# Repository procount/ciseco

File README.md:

# ciseco
Ciseo XRF documentation from the wirelessthings.net website, which has sadly closed.

Cisecostuff-2013 fodler kindly provided by Alvar Kusma
Alvar Kusma <alvar@raamat.polva.ee>

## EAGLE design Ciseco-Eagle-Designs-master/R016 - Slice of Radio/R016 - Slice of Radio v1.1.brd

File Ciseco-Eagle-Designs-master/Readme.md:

This repository contains the schematic and pcb files for some Ciseco products

Each product is in its own folder and there may be any combination of files from.
* PDF schematic
* Eagle schematic
* Eagle PCB
* Gerbers

If you wish to download all the files either use git clone

    $ git clone https://github.com/CisecoPlc/Ciseco-Eagle-Designs.git

or download them all as zip file

https://github.com/CisecoPlc/Ciseco-Eagle-Designs/archive/master.zip

To download individual files navigate to the file and select 'Raw' from the toolbar, then use your browsers File->Save As option

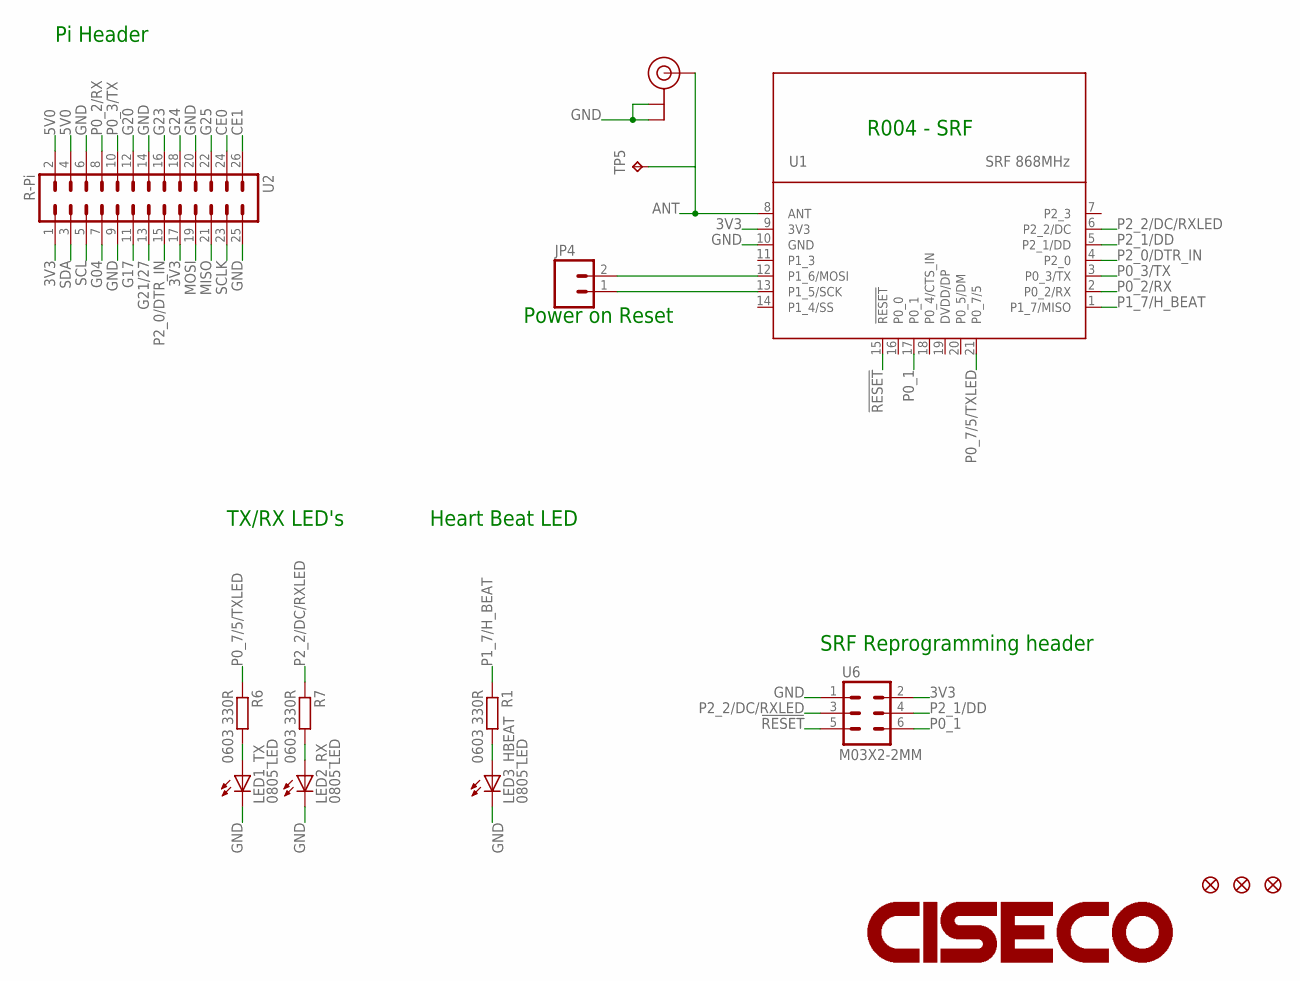
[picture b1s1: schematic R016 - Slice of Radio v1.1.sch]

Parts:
JP1, JP2, JP3: FIDUCIAL1X2.5-STOP; FIDUCIAL-1X2.5-STOP
JP4: M02PTH; 1X02
LED1_TX, LED2_RX, LED3_HBEAT: 0805 LED; LED-0805-CORRECT
LOGO1: CISECOLOGO-2MM; CISECO-2MM
R1, R6, R7: 0603 330R; C0603K-SMALL
TP5: TPPAD1-13; P1-13
U1: SRF 868MHz; SRF-LANDING-1.2
U2: R-Pi; EVE-BOARD-REF-LOCK
U6: M03X2-2MM; 2X3_2MM
U11: U.FL 868; U.FL

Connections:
3V3: U1.9 (3V3), U2.1, U2.17, U6.2
5V0: U2.2, U2.4
!RESET: U1.15 (!RESET), U6.5
ANT: TP5.TP, U1.8 (ANT), U11.P$3 (SIGNAL)
CE0: U2.24
CE1: U2.26
G04: U2.7
G17: U2.11
G20: U2.12
G21/27: U2.13
G23: U2.16
G24: U2.18
G25: U2.22
GND: LED1_TX.C, LED2_RX.C, LED3_HBEAT.C, U1.10 (GND), U2.6, U2.9, U2.14, U2.20, U2.25, U6.1, U11.P$1 (GND), U11.P$2 (GND)
MISO: U2.21
MOSI: U2.19
unnamed: LED3_HBEAT.A, R1.2
unnamed: JP4.1, U1.13 (P1_5/SCK)
unnamed: JP4.2, U1.12 (P1_6/MOSI)
unnamed: LED2_RX.A, R7.2
unnamed: LED1_TX.A, R6.2
P0_1: U1.17 (P0_1), U6.6
P0_2/RX: U1.2 (P0_2/RX), U2.8
P0_3/TX: U1.3 (P0_3/TX), U2.10
P0_7/5/TXLED: R6.1, U1.21 (P0_7/5)
P1_7/H_BEAT: R1.1, U1.1 (P1_7/MISO)
P2_0/DTR_IN: U1.4 (P2_0), U2.15
P2_1/DD: U1.5 (P2_1/DD), U6.4
P2_2/DC/RXLED: R7.1, U1.6 (P2_2/DC), U6.3
SCL: U2.5
SCLK: U2.23
SDA: U2.3

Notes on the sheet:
Power on Reset
Pi Header
SRF Reprogramming header
TX/RX LED's
Heart Beat LED
R004 - SRF

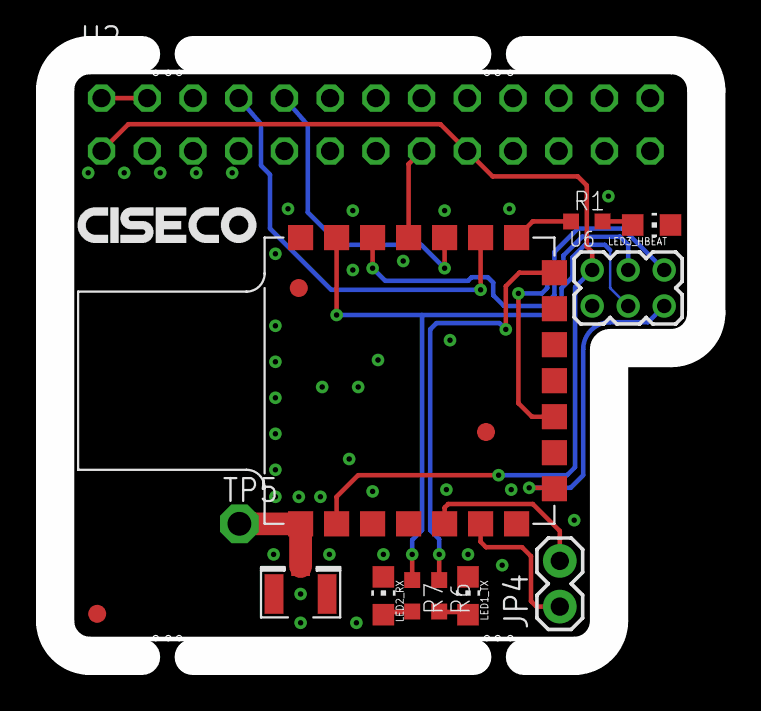
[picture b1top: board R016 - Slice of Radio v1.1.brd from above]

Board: 2 copper layers, 36.3 x 33.5 mm, 18 parts (1 on the bottom side), 18 nets.

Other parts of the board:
U$4: WEEE-LOGO
U$5: PIBOW

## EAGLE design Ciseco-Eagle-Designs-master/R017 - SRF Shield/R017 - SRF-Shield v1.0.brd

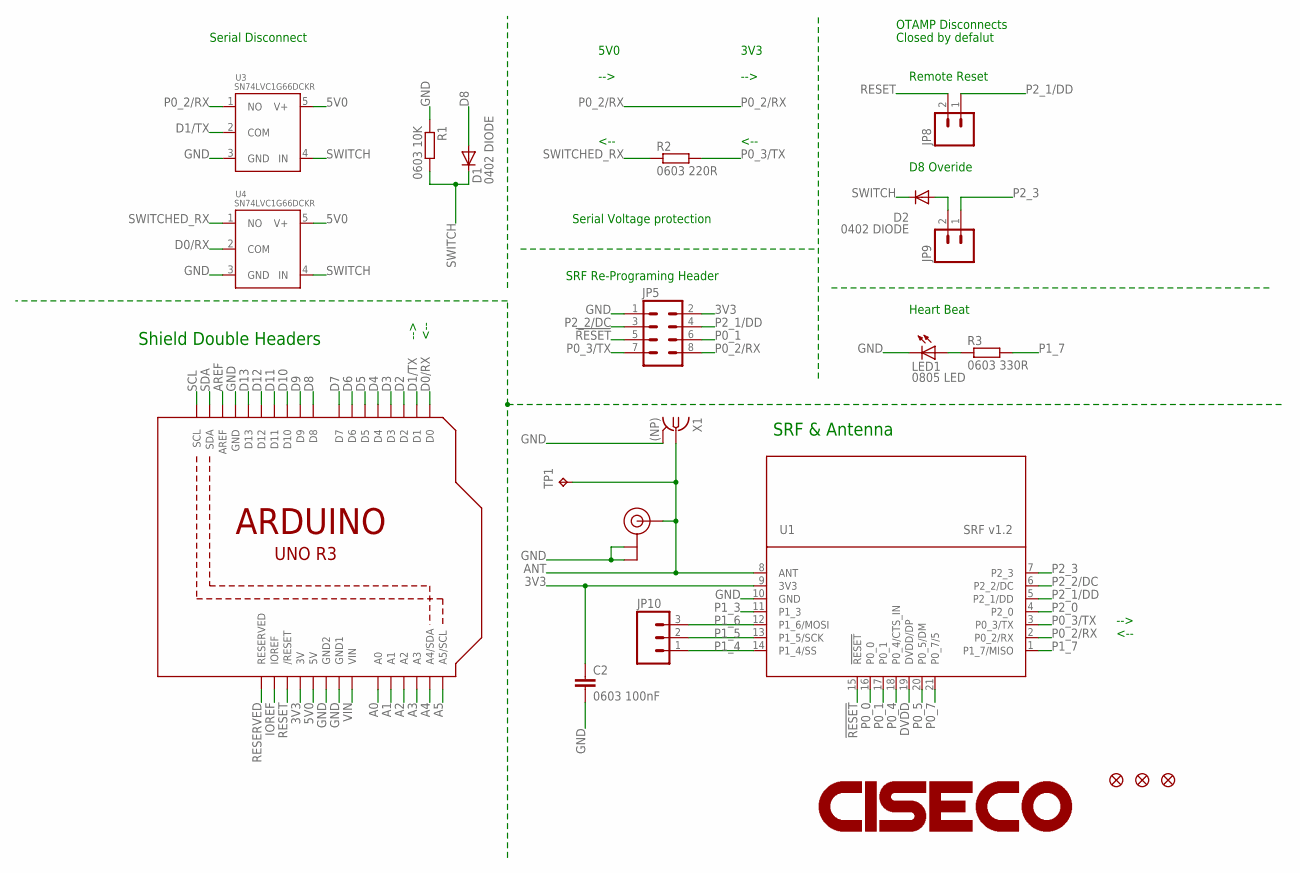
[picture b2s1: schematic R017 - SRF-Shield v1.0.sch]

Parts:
C2: 0603 100nF; C0402-NARROW
D1, D2: 0402 DIODE; D0402-NARROW
JP4, JP6, JP7: FIDUCIAL1X2.5-STOP; FIDUCIAL-1X2.5-STOP
JP5: M04X2; 2X4
JP8, JP9: M02PTH; 1X02
JP10: M03PTH; 1X03
LED1: 0805 LED; LED-0805-1206
R1: 0603 10K; C0603K-SMALL
R2: 0603 220R; C0603K-SMALL
R3: 0603 330R; C0603K-SMALL
TP1: TPPAD1-13; P1-13
U1: SRF v1.2; SRF-LANDING-1.0A-MOVE
U2: ARDUINOR3-DOUBL-OFFSET; ARDUINOR3-DOUBLE-OFFSET
U3, U4: SN74LVC1G66DCKR; SC70
U5: U.FL (NP); U.FL
U$3: CISECO-LARGE; CISECO-4MM
X1: (NP); J502-ND-142-0711-821/826-LWK1

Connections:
3V3: C2.1, JP5.2, U1.9 (3V3), U2.3V, U2.3V1 (3V)
5V0: U2.5V, U2.5V1 (5V), U3.5 (V+), U4.5 (V+)
!RESET: JP5.5, U1.15 (!RESET)
A0: U2.A0, U2.A6 (A0)
A1: U2.A1, U2.A7 (A1)
A2: U2.A2, U2.A8 (A2)
A3: U2.A3, U2.A9 (A3)
A4: U2.A4 (A4/SDA), U2.A10 (A4/SDA)
A5: U2.A5 (A5/SCL), U2.A11 (A5/SCL)
ANT: TP1.TP, U1.8 (ANT), U5.P$3 (SIGNAL), X1.1
AREF: U2.AREF, U2.AREF1 (AREF)
D0/RX: U2.D0, U2.D18 (D0), U4.2 (COM)
D1/TX: U2.D1, U2.D17 (D1), U3.2 (COM)
D2: U2.D2, U2.D16 (D2)
D3: U2.D3, U2.D15 (D3)
D4: U2.D4, U2.D14 (D4)
D5: U2.D5, U2.D19 (D5)
D6: U2.D6, U2.D20 (D6)
D7: U2.D7, U2.D21 (D7)
D8: D1.A, U2.D8, U2.D22 (D8)
D9: U2.D9, U2.D23 (D9)
D10: U2.D10, U2.D24 (D10)
D11: U2.D11, U2.D25 (D11)
D12: U2.D12, U2.D26 (D12)
D13: U2.D13, U2.D27 (D13)
DVDD: U1.19 (DVDD/DP)
GND: C2.2, JP5.1, LED1.C, R1.1, U1.10 (GND), U2.GND, U2.GND1, U2.GND2, U2.GND3 (GND1), U2.GND4 (GND2), U2.GND5 (GND), U3.3 (GND), U4.3 (GND), U5.P$1 (GND), U5.P$2 (GND), X1.G@1 (GND), X1.G@2 (GND), X1.G@3 (GND), X1.G@4 (GND)
IOREF: U2.IOREF, U2.IOREF1 (IOREF)
unnamed: LED1.A, R3.1
OTAMP_M: D2.A, JP9.2
P0_0: U1.16 (P0_0)
P0_1: JP5.6, U1.17 (P0_1)
P0_2/RX: JP5.8, U1.2 (P0_2/RX), U3.1 (NO)
P0_3/TX: JP5.7, R2.2, U1.3 (P0_3/TX)
P0_4: U1.18 (P0_4/CTS_IN)
P0_5: U1.20 (P0_5/DM)
P0_7: U1.21 (P0_7/5)
P1_3: U1.11 (P1_3)
P1_4: JP10.1, U1.14 (P1_4/SS)
P1_5: JP10.2, U1.13 (P1_5/SCK)
P1_6: JP10.3, U1.12 (P1_6/MOSI)
P1_7: R3.2, U1.1 (P1_7/MISO)
P2_0: U1.4 (P2_0)
P2_1/DD: JP5.4, JP8.1, U1.5 (P2_1/DD)
P2_2/DC: JP5.3, U1.6 (P2_2/DC)
P2_3: JP9.1, U1.7 (P2_3)
RESERVED: U2.RESERVED, U2.RESERVED1 (RESERVED)
RESET: JP8.2, U2.RESET (/RESET), U2.RESET1 (/RESET)
SCL: U2.SCL, U2.SCL1 (SCL)
SDA: U2.SDA, U2.SDA1 (SDA)
SWITCH: D1.C, D2.C, R1.2, U3.4 (IN), U4.4 (IN)
SWITCHED_RX: R2.1, U4.1 (NO)
VIN: U2.VIN, U2.VIN1 (VIN)

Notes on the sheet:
SRF Re-Programing Header
5V0
3V3
Remote Reset
Heart Beat
Closed by defalut
OTAMP Disconnects
Serial Voltage protection
Serial Disconnect
<--
-->
D8 Overide
Shield Double Headers
SRF & Antenna

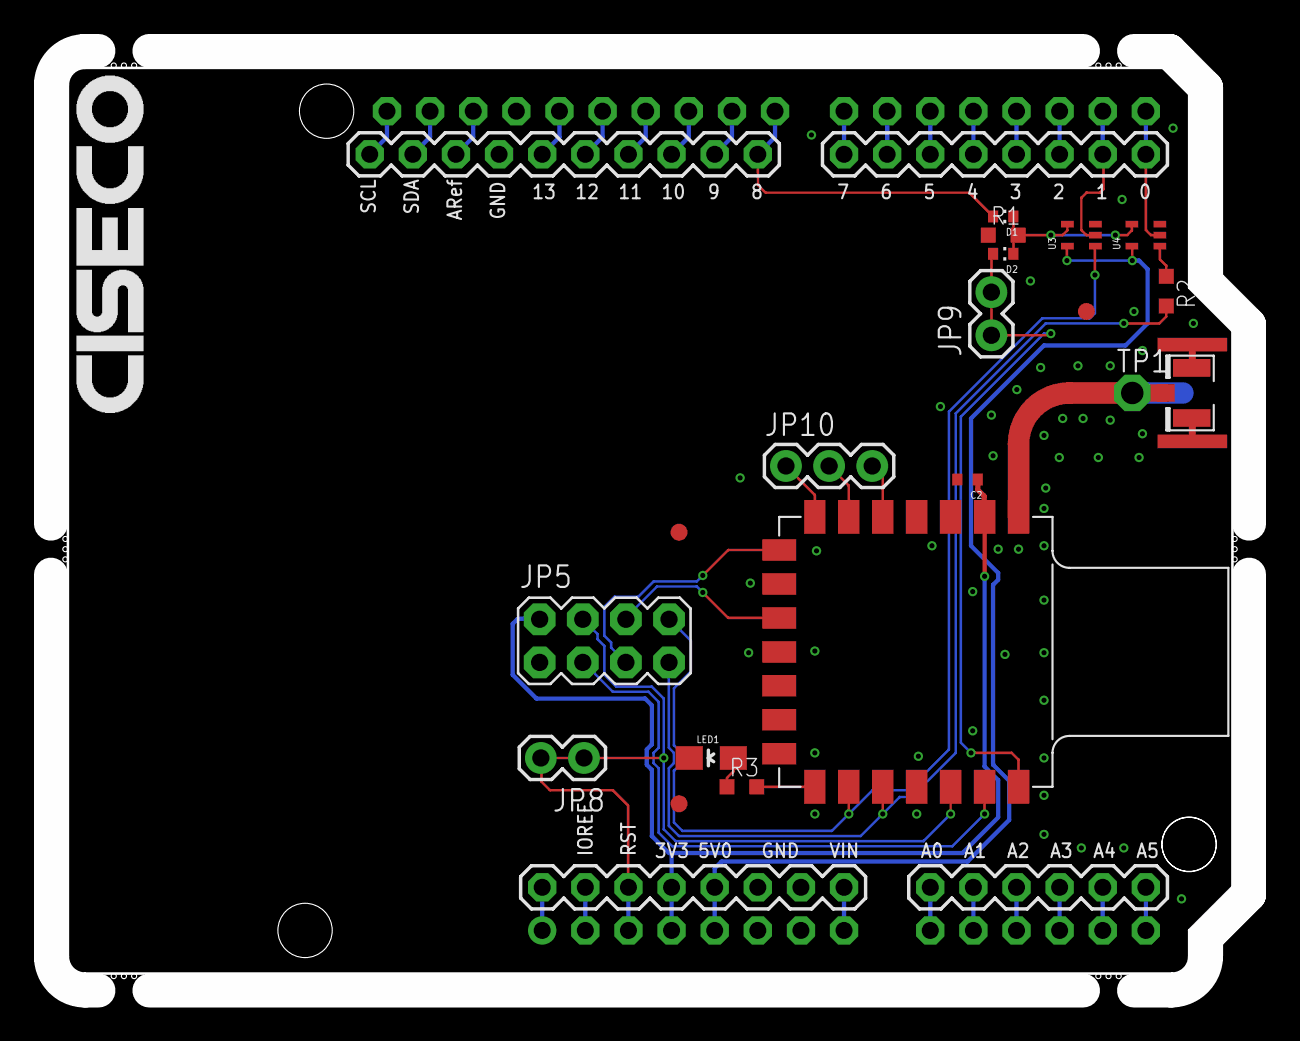
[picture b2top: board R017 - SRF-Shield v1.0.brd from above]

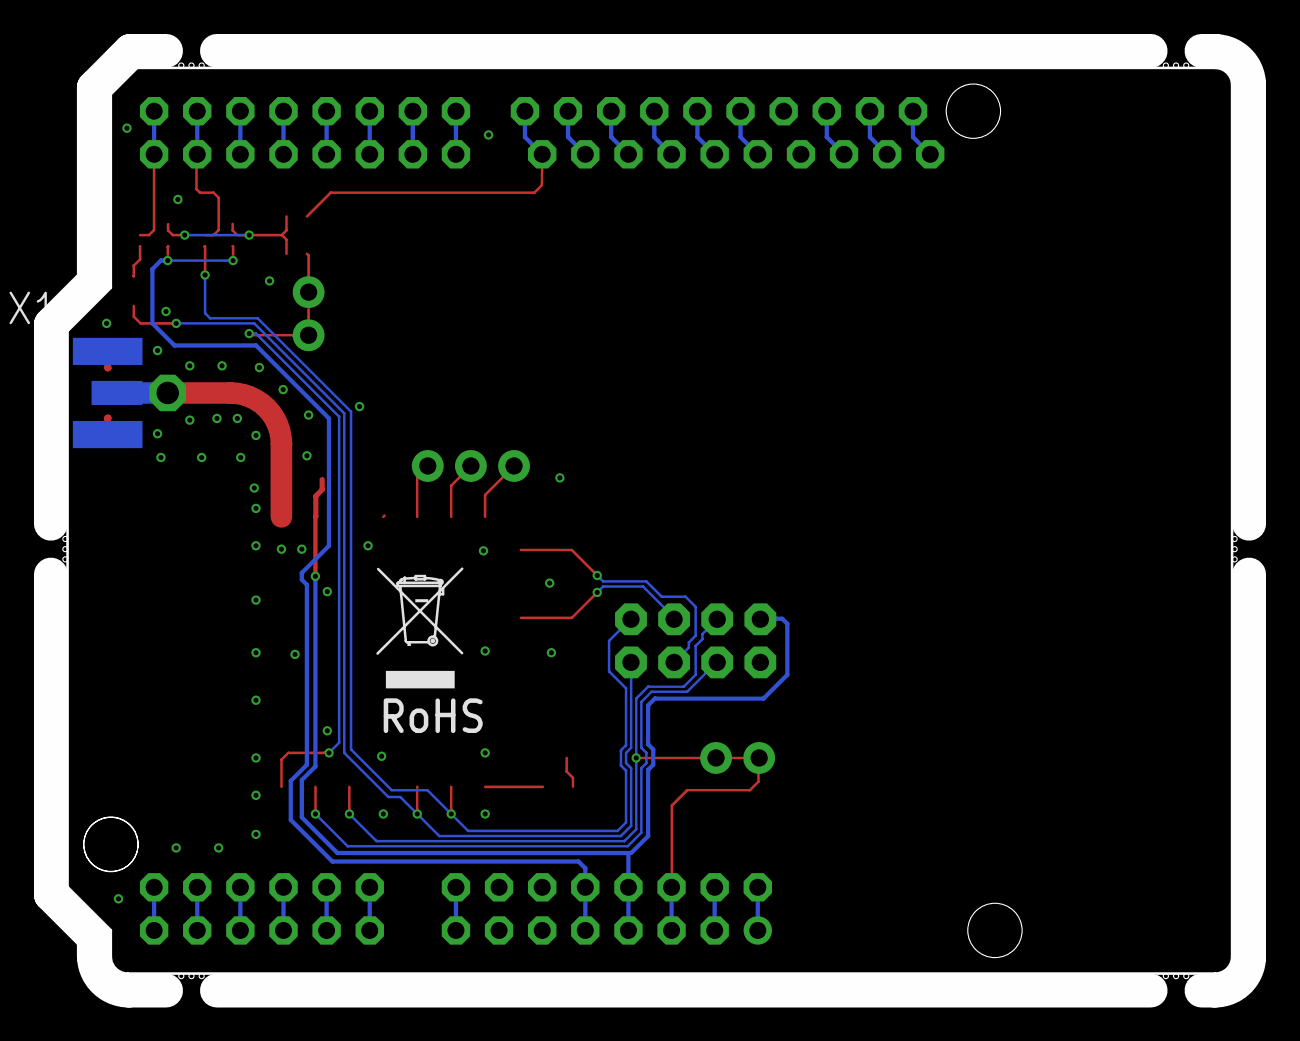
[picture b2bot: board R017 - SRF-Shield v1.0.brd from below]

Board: 2 copper layers, 70.6 x 55.4 mm, 23 parts (2 on the bottom side), 46 nets.

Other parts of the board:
U$6: WEEE-LOGO

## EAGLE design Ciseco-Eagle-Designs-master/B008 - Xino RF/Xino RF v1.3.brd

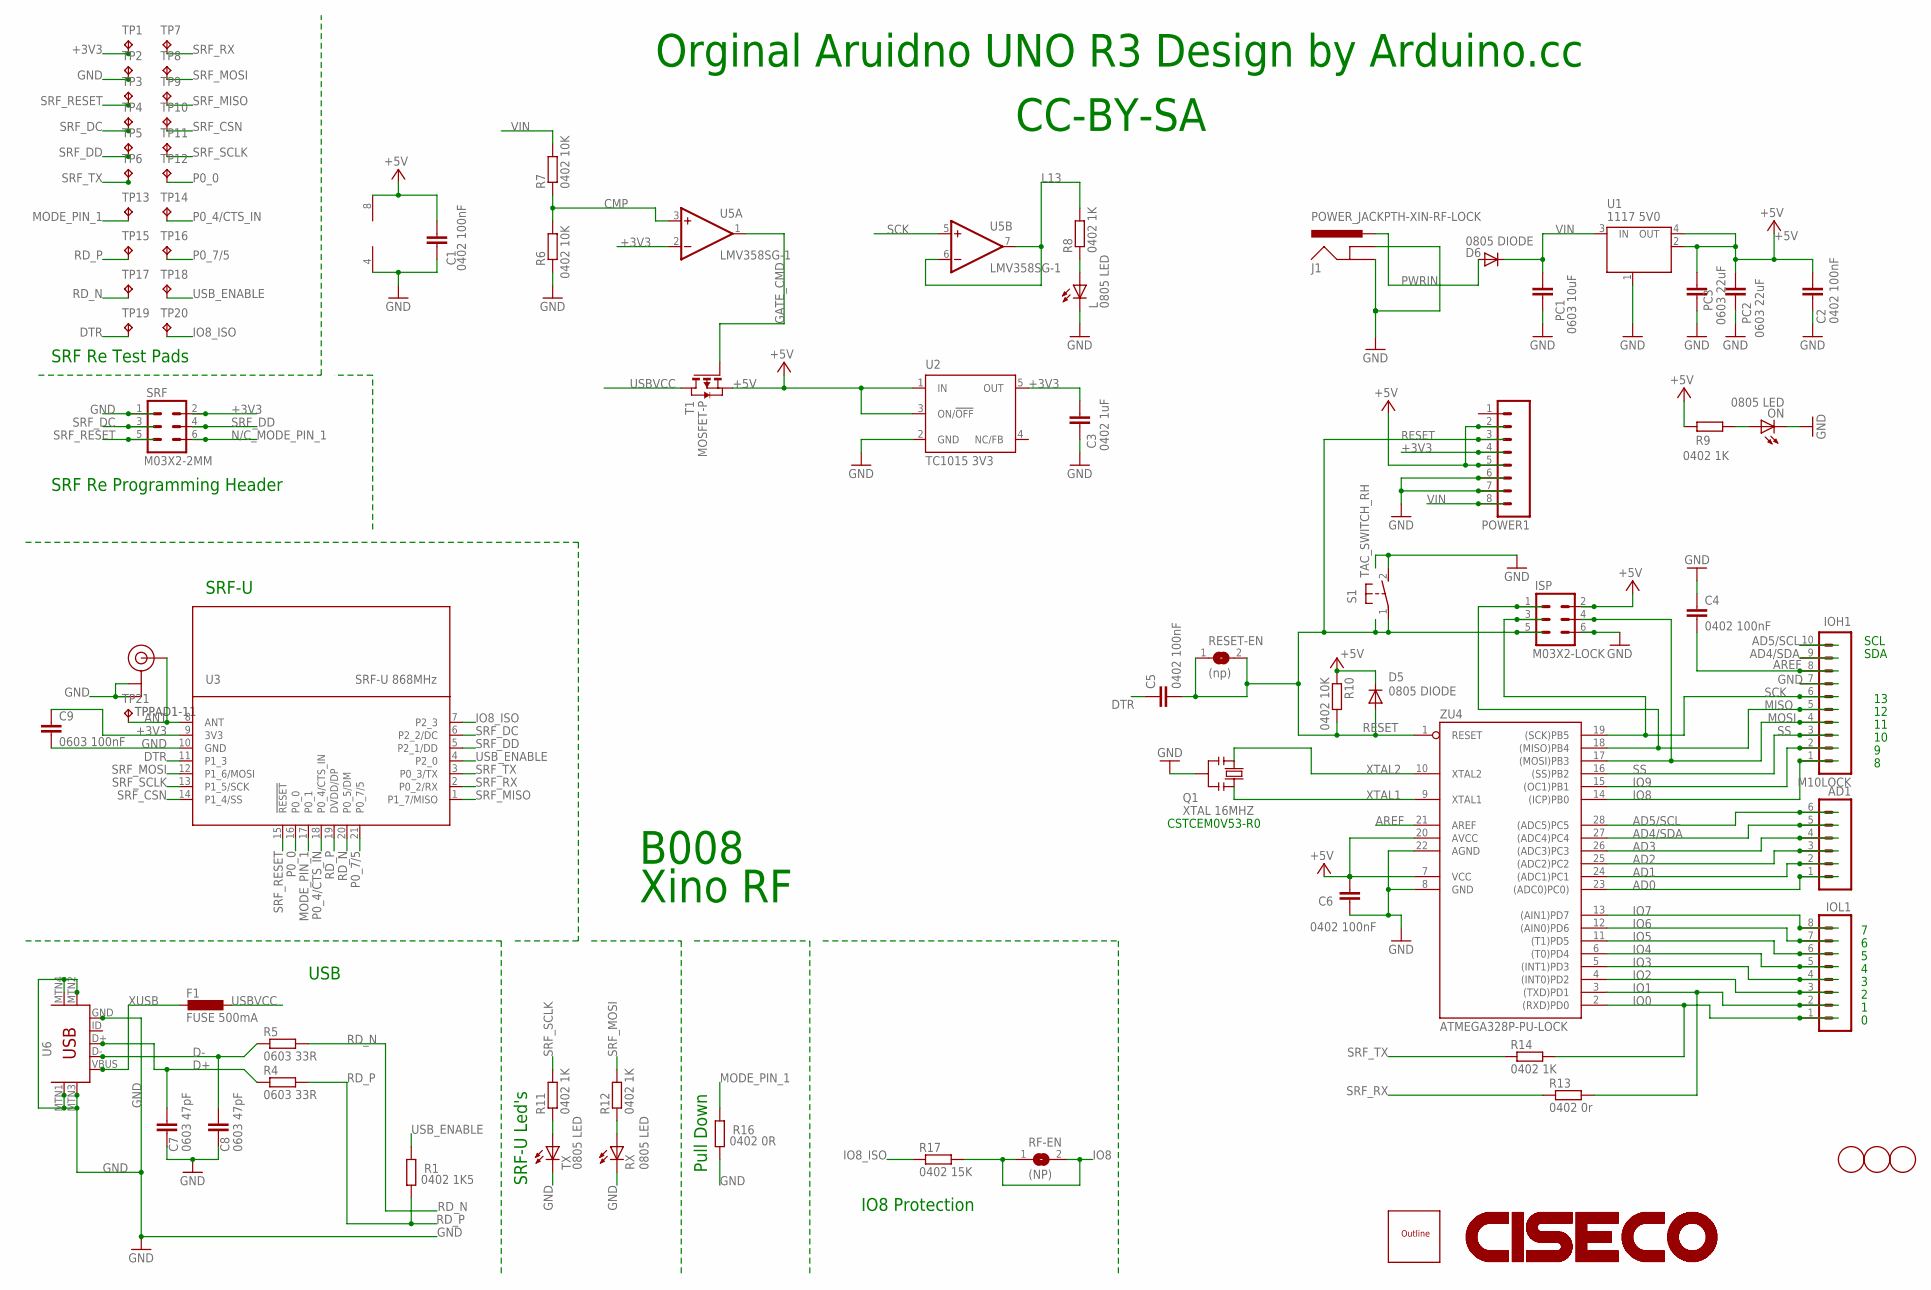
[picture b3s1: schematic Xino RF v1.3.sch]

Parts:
AD1: M06LOCK; 1X06_LOCK
C1, C2, C4, C5: 0402 100nF; C0402-SMALLER
C3: 0402 1uF; C0402-SMALLER
C6: 0402 100nF; C0603-ROUND
C7, C8: 0603 47pF; C0603K-SMALL
C9: 0603 100nF; C0402-SMALLER
D5, D6: 0805 DIODE; 0805-DIODE
F1: FUSE 500mA; L1812
FD1, FD2, FD3: FIDUCIALMOUNT; FIDUCIA-MOUNT
IOH1: M10LOCK; 1X10_LOCK
IOL1: M08LOCK; 1X08_LOCK
ISP: M03X2-LOCK; 2X3_LOCK
J1: POWER_JACKPTH-XIN-RF-LOCK; POWER_JACK_PTH_XINO_RF_LOCK
L: 0805 LED; LED-0805-1206
ON: 0805 LED; LED-0805-1206
PC1: 0603 10uF; C0805K
PC2, PC3: 0603 22uF; C0805K
POWER1: M08LOCK; 1X08_LOCK
Q1: XTAL 16MHZ; RESONATOR
R1: 0402 1K5; R0402-SMALLER
R4, R5: 0603 33R; C0603K-SMALL
R6, R7, R10: 0402 10K; R0402-SMALLER
R8, R9, R11, R12, R14: 0402 1K; R0402-SMALLER
R13: 0402 0r; R0402-SMALLER
R16: 0402 0R; R0402-SMALLER
R17: 0402 15K; R0402-SMALLER
RESET-EN: (np); SJ
RF-EN: (NP); SJ
RX: 0805 LED; LED-0805-1206
S1: TAC_SWITCH_RH; B3F-31XX
SRF: M03X2-2MM; 2X3_2MM
T1: MOSFET-P; SOT-23
TP1, TP2, TP3, TP4, TP5, TP6, TP7, TP8, TP9, TP10, TP11, TP12, TP13, TP14, TP15, TP16, TP17, TP18, TP19, TP20: TPB1,27; B1,27
TP21: TPPAD1-11; P1-11
TX: 0805 LED; LED-0805-1206
U1: 1117 5V0; SOT223
U2: TC1015 3V3; SOT23-DBV
U3: SRF-U 868MHz; SRF-LANDING-1.2
U5: LMV358SG-1; SO08
U6: USB-MINIB-5PIN; USB-MINIB-CISECO-1
U11: U.FL 868; U.FL
U$1: CISECO-MEDIUM; CISECO-1.3MM
U$2: ARDUINO-OUTLINE-MILL
U$3: CISECO-LARGE; CISECO-4MM
ZU4: ATMEGA328P-PU-LOCK; DIL28-3-LOCK

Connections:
+3V3: C3.2, C9.1, POWER1.4, SRF.2, TP1.TP, U2.5 (OUT), U3.9 (3V3), U5.2 (-IN)
+5V: C1.2, C2.2, C6.2, D5.C, ISP.2, PC2.1, PC3.1, POWER1.2, POWER1.5, R9.2, R10.1, T1.2 (S), U1.2 (OUT), U1.4 (OUT), U2.1 (IN), U2.3 (ON/!OFF), U5.8 (V+), ZU4.7 (VCC), ZU4.20 (AVCC)
AD0: AD1.1, ZU4.23 ((ADC0)PC0))
AD1: AD1.2, ZU4.24 ((ADC1)PC1)
AD2: AD1.3, ZU4.25 ((ADC2)PC2)
AD3: AD1.4, ZU4.26 ((ADC3)PC3)
AD4/SDA: AD1.5, IOH1.9, ZU4.27 ((ADC4)PC4)
AD5/SCL: AD1.6, IOH1.10, ZU4.28 ((ADC5)PC5)
ANT: TP21.TP, U3.8 (ANT), U11.P$3 (SIGNAL)
AREF: C4.2, IOH1.8, ZU4.21 (AREF)
CMP: R6.2, R7.1, U5.3 (+IN)
D+: C7.1, R4.1, U6.D+
D-: C8.1, R5.1, U6.D-
DTR: C5.1, TP19.TP, U3.11 (P1_3)
GATE_CMD: T1.3 (G), U5.1 (OUT)
GND: C1.1, C2.1, C3.1, C4.1, C6.1, C7.2, C8.2, C9.2, IOH1.7, ISP.6, J1.GND, J1.GNDBREAK, L.C, ON.C, PC1.2, PC2.2, PC3.2, POWER1.6, POWER1.7, Q1.2, R6.1, R16.1, RX.C, S1.2 (S), SRF.1, TP2.TP, TX.C, U1.1 (GND/ADJ), U2.2 (GND), U3.10 (GND), U5.4 (V-), U6.GND, U6.MTN1 (MTN2), U6.MTN2 (MTN3), U6.MTN3 (MTN1), U6.MTN4, U11.P$1 (GND), U11.P$2 (GND), ZU4.8 (GND), ZU4.22 (AGND)
IO0: IOL1.1, R14.2, ZU4.2 ((RXD)PD0)
IO1: IOL1.2, R13.2, ZU4.3 ((TXD)PD1)
IO2: IOL1.3, ZU4.4 ((INT0)PD2)
IO3: IOL1.4, ZU4.5 ((INT1)PD3)
IO4: IOL1.5, ZU4.6 ((T0)PD4)
IO5: IOL1.6, ZU4.11 ((T1)PD5)
IO6: IOL1.7, ZU4.12 ((AIN0)PD6)
IO7: IOL1.8, ZU4.13 ((AIN1)PD7)
IO8: IOH1.1, R17.2, RF-EN.1, RF-EN.2, ZU4.14 ((ICP)PB0)
IO8_ISO: R17.1, TP20.TP, U3.7 (P2_3)
IO9: IOH1.2, ZU4.15 ((OC1)PB1)
L13: R8.2, U5.6 (-IN), U5.7 (OUT)
MISO: IOH1.5, ISP.1, ZU4.18 ((MISO)PB4)
MODE_PIN_1: R16.2, TP13.TP, U3.17 (P0_1)
MOSI: IOH1.4, ISP.4, ZU4.17 ((MOSI)PB3)
unnamed: L.A, R8.1
unnamed: ON.A, R9.1
unnamed: R12.1, RX.A
unnamed: R11.1, TX.A
N/C_MODE_PIN_1: SRF.6
P0_0: TP12.TP, U3.16 (P0_0)
P0_4/CTS_IN: TP14.TP, U3.18 (P0_4/CTS_IN)
P0_7/5: TP16.TP, U3.21 (P0_7/5)
PWRIN: D6.A, J1.PWR
RD_N: R5.2, TP17.TP, U3.20 (P0_5/DM)
RD_P: R1.1, R4.2, TP15.TP, U3.19 (DVDD/DP)
RESET: C5.2, D5.A, ISP.5, POWER1.3, R10.2, RESET-EN.1, RESET-EN.2, S1.1, ZU4.1 (RESET)
SCK: IOH1.6, ISP.3, U5.5 (+IN), ZU4.19 ((SCK)PB5)
SRF_CSN: TP10.TP, U3.14 (P1_4/SS)
SRF_DC: SRF.3, TP4.TP, U3.6 (P2_2/DC)
SRF_DD: SRF.4, TP5.TP, U3.5 (P2_1/DD)
SRF_MISO: TP9.TP, U3.1 (P1_7/MISO)
SRF_MOSI: R12.2, TP8.TP, U3.12 (P1_6/MOSI)
SRF_RESET: SRF.5, TP3.TP, U3.15 (!RESET)
SRF_RX: R13.1, TP7.TP, U3.2 (P0_2/RX)
SRF_SCLK: R11.2, TP11.TP, U3.13 (P1_5/SCK)
SRF_TX: R14.1, TP6.TP, U3.3 (P0_3/TX)
SS: IOH1.3, ZU4.16 ((SS)PB2)
USBVCC: F1.1, T1.1 (D)
USB_ENABLE: R1.2, TP18.TP, U3.4 (P2_0)
VIN: D6.C, PC1.1, POWER1.8, R7.2, U1.3 (IN)
XTAL1: Q1.3, ZU4.9 (XTAL1)
XTAL2: Q1.1, ZU4.10 (XTAL2)
XUSB: F1.2, U6.VBUS

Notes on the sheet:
Xino RF
SDA
SCL
Pull Down
IO8 Protection
CC-BY-SA
Orginal Aruidno UNO R3 Design by Arduino.cc
USB
SRF Re Programming Header
SRF Re Test Pads
SRF-U
SRF-U Led's
B008
CSTCEM0V53-R0

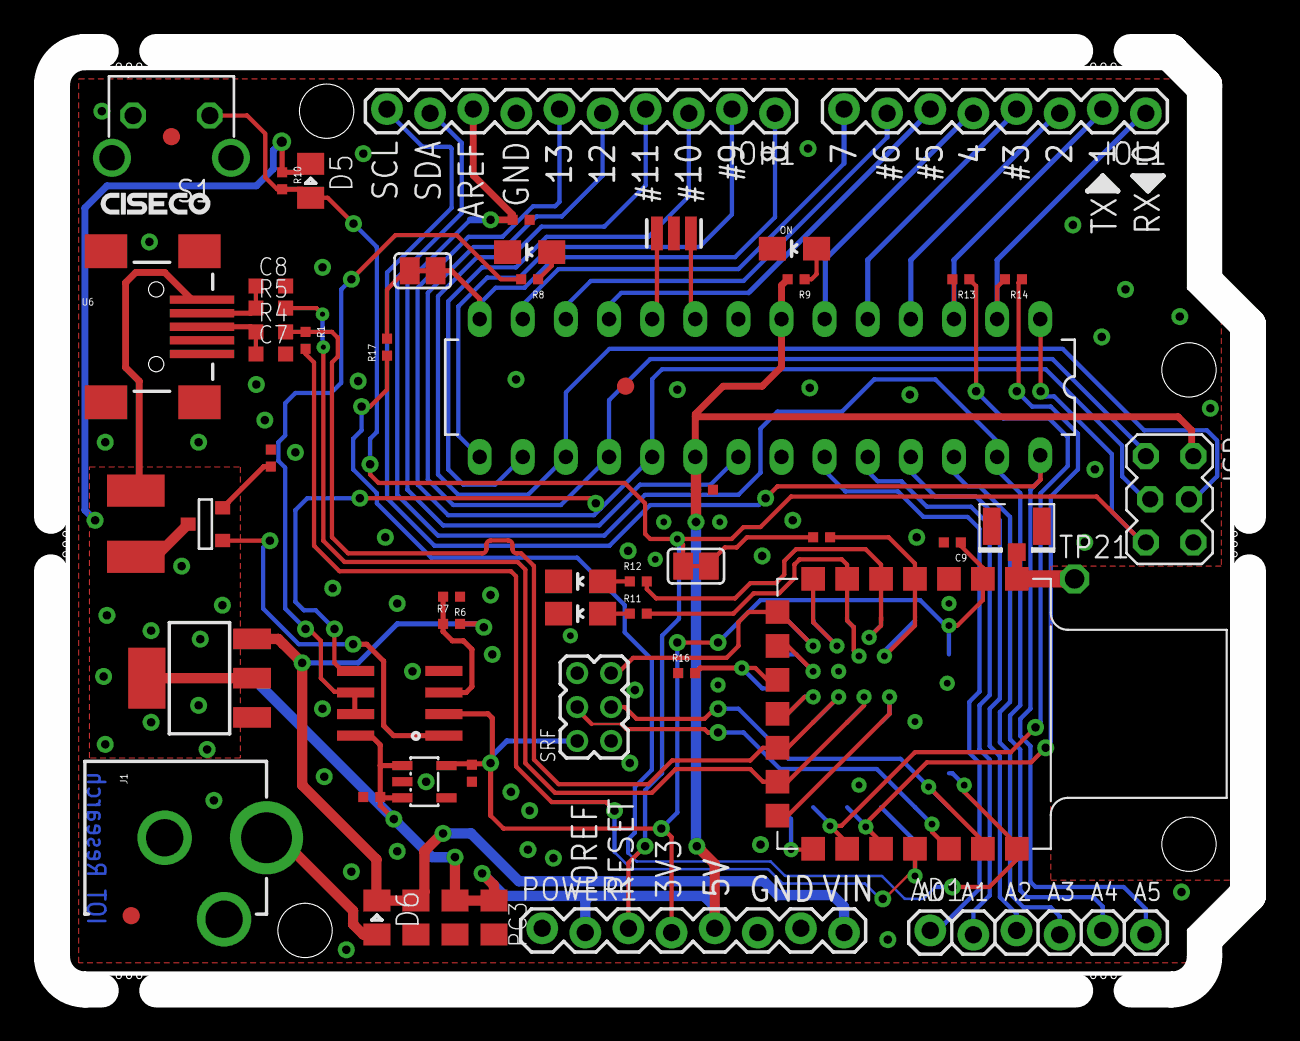
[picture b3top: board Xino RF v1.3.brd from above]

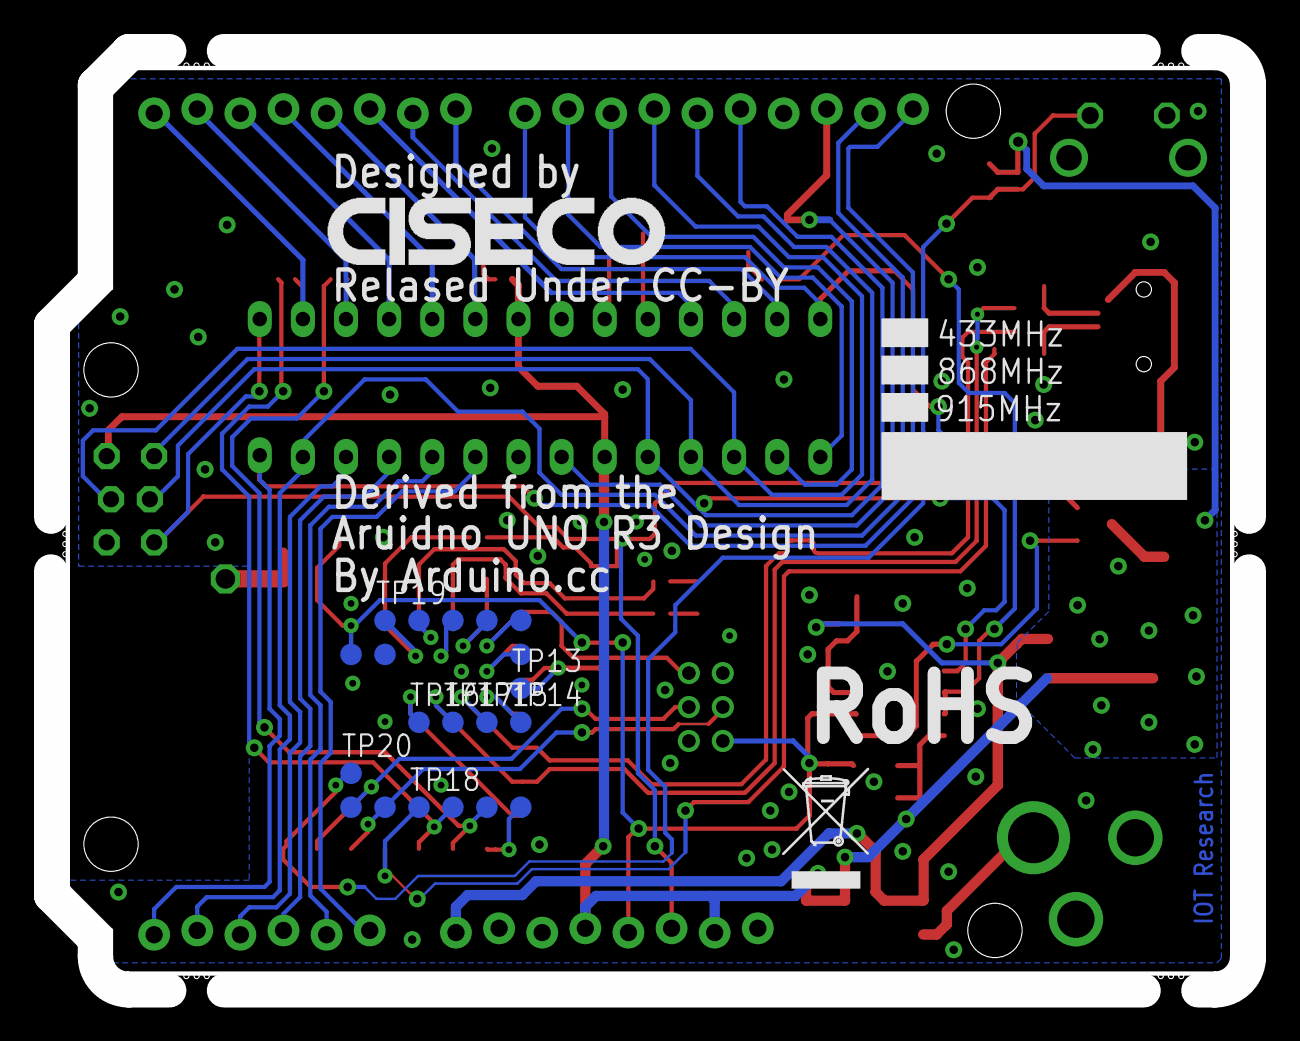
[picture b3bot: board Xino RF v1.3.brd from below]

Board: 2 copper layers, 70.6 x 55.4 mm, 80 parts (22 on the bottom side), 59 nets.

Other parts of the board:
U$4: WEEE-LOGO

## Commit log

2020-11-27 Added Cisecostuff-2013

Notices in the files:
Ciseco-Eagle-Designs-master/B008 - Xino RF/Xino RF v1.3.brd:
Relased Under CC-BY
parts and their libraries:
SparkFunJan12: Licensing: CC v3.0 Share-Alike You are welcome to use this library for commercial purposes.
